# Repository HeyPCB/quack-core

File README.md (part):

# Quack Core

The brain board for the Open Duck Mini: a Pi Zero 2W carrier with the 14-servo STS bus, a fused and switched 2S power path laid in stitched copper zones, USB-C charging with balancing, and the IMU.

Part of [HeyPCB's open robot boards](https://github.com/HeyPCB). Designed end to end with the HeyPCB method on
KiCad 10 (headless pipeline, Freerouting 2.4.1); every number below is measured on the files in this repository.
Mentions of `./run.sh`, `docs/rules/`, `blocks/` or `parts/` refer to the heypcb-kicad SDK that produced them.

| Layers | Outline | Parts | Nets | Connections routed | Vias | ERC errors | DRC errors / unconnected / parity |
|---|---|---|---|---|---|---|---|
| 4 | 101 x 51.5 mm | 138 | 78 | 312 -> 0 open | 224 | 0 | 0 / 0 / 0 |

**Not fabricated, assembled or powered.**

| | |
|---|---|
| KiCad project | [`kicad/`](kicad/) |
| Gerbers (unzipped and zipped), BOM, CPL, STEP, schematic PDF | [`fab/`](fab/) |
| Printed parts (STEP/STL), CadQuery source, fit report | [`cad/`](cad/) |
| Renders | [top](media/top.png), [bottom](media/bottom.png) |
| Design process, every step as KiCad rendered it | [`media/design-process.mp4`](media/design-process.mp4) |

Quack Core is a brain board for the Open Duck Mini (v2), the open-source miniature biped by Antoine
Pirrone and contributors. It is a carrier for a Raspberry Pi Zero 2 W and it bolts onto the four
existing `trunk_top` bosses in the duck's rear bay. It takes the 2S pack through a 20 A fuse, a
1 mOhm shunt and a back-to-back P-FET switch, drives the STS3215 servo bus, and charges and balances
the pack from USB-C. It was designed with the HeyPCB method on KiCad 10 (10.0.6), by heypcb-kicad's
headless pipeline with Freerouting 2.4.1, from the brief in `board.json` and the research spec
`robots/research/duck/spec.md` (Option A).

**This board has not been fabricated, assembled or powered.** Everything below is what KiCad, the
pipeline and the CAD scripts measured on the design files. Nothing here has been tested on
hardware or in the robot, and nothing here contains or tests software.

## Specs

- **Pi Zero 2 W carrier.** The Pi plugs in face-up on a 2x20 SMD socket (PM254-2-20-S-8.5,
  C3975165), 8.5 mm tall, on four M2.5 standoffs (not supplied) on its 58 x 23 mm hole pattern.
  The board's 5.1 V back-powers the Pi through header pins 2 and 4. Do not also plug the Pi's PWR
  micro-USB.
- **Pack input:** a vertical XT30 (J2), an SMAJ10CA bidirectional TVS (D1), a 20 A Littelfuse
  NANO2 (F1, 0451020.MRL) and a 1 mOhm 3 W 2512 shunt (R1). An INA226 at 0x40 reads the shunt and
  the pack voltage; its ALERT goes to GPIO4 and to the servo-kill latch.
- **Main switch:** two AON6411 P-FETs, source to source (Q1, Q2). The robot's existing backpack
  slide switch is re-used as a logic switch on J5 and carries about 80 uA. A reversed pack leaves
  both FETs off.
- **Servo power:** a third AON6411 (Q3) switches VSYS onto VSERVO. It is on by default: GPIO26 (with
  a 100 k pull-down) or a latched INA226 ALERT turns it off. VSERVO has 2 x 470 uF / 16 V bulk
  (C10, C11) and 10 uF plus an ESD5Z5.0 on DATA at each port.
- **Servo bus:** an exact copy of the Waveshare Bus Servo Adapter (A) / Feetech reference half-duplex
  driver (74LVC1G126 + 74LVC1G125 + MMBT3906) on the Pi's PL011 UART (GPIO14/15), with the
  spec's additions: 0 ohm source-select links, a J16 header for an external USB-UART, a DNP RTS
  link, a DNP DATA pull-up and four DNP test pads.
- **Servo ports:** four 5264-type 3-pin headers (HC-5264-3A, C2845815), DATA / VSERVO / GND: J6 left
  leg, J7 right leg, J8 neck chain, J9 spare.
- **Pi rail:** an LM74700 + AO3400A ideal diode with 470 uF hold-up behind the 5 A face/aux fuse
  (F2), then a TPS56339 3 A buck to 5.10 V (53.6 k / 10 k on a 0.802 V reference) and an XC6206
  3.3 V LDO for the board's logic.
- **Charger:** BQ25887 2S boost charger from USB-C (J4, HRO TYPE-C-31-M-12, 5.1 k on each CC, a plain
  sink) through a 2 A PTC (F4), with cell balancing through the balance lead's mid tap (J3 pin 2).
  Input limit 1.48 A (750 ohm on ILIM). It taps the pack ahead of the switch through a 5 A NANO2
  (F3), so it charges with the robot switched off. Orange CHG LED, /INT to GPIO16.
- **IMU:** BNO055 at 0x28 (fitted) and a BMI088 footprint at 0x18/0x68 (not fitted).
- **Face link** (the shared contract with the Quack Face board, spec 4.5): J12 JST-GH 12P top entry,
  J13 JST-XH 2P with the fused battery rail.
- **Other I/O:** foot switches on J10/J11 (JST-PH 2P, 1 k / 100 nF RC and ESD), a Qwiic port (J14,
  JST-SH 4P top entry, 3.3 V), green 5V LED, red LED1/LED2 on GPIO5/GPIO6.
- **Board:** 101 x 51.5 mm (CAD x -93.5 to -42.0, y -50.5 to +50.5), 1.6 mm, 4 copper layers.
  F.Cu signal with a GND pour, In1 a GND plane, In2 signal with a VSERVO pour, B.Cu signal with a
  GND pour, and the power path laid as stitched copper zones on F.Cu, In2 and B.Cu (see *Power
  zones*). Single-sided assembly. Four non-plated 2.7 mm holes for M2.5 screws on the bosses, and
  four more for the Pi's standoffs. The front edge is notched 0.8 mm between CAD y -28.25 and
  +28.25 to clear the `trunk_top` chamfer (see *CAD fit*).

## Option A: the Pi moves into the body

Today the Pi Zero 2 W, its 5 V UBEC and the amplifier sit on the head's ceiling, and a harness
through the 4-DOF neck carries 7.4 V, USB, I2C and the foot-switch wires down to the body (spec
1.4). Quack Core takes the research spec's Option A (spec 2.6): the Pi plugs into this board, in the
body, next to the battery, the servo bus, the IMU and the foot switches. What that changes:

- **Update the URDF masses before retraining.** The Pi (about 10 g) and the UBEC (about 15 g,
  replaced here by the on-board buck) leave the head and join the trunk. Both figures are the
  spec's estimates. The walk policy was trained on the URDF's mass properties (`head_assembly`
  352.6 g, `trunk_assembly` 698.5 g), so update both links, add this board's own mass to the trunk,
  and retrain (spec 2.6, 7). This board's mass was not measured.
- **Camera.** CSI would have to cross the +/-160 degree head-yaw joint. Either run a round
  CSI-to-HDMI extension through the neck (Arducam B0091, with a 22-to-15-pin cable at the Pi), or
  leave the camera off. The walk runtime does not use it (spec 2.6).
- **Runtime: configuration only** (spec 3.10). No Python changes:
  1. `/boot/firmware/config.txt`: `enable_uart=1` and `dtoverlay=miniuart-bt`. The PL011 moves to
     GPIO14/15 and Bluetooth stays up for the gamepad. 1 Mbps is 48 MHz / 16 / 3 exactly.
  2. `cmdline.txt`: remove `console=serial0,115200`.
  3. A udev rule, `KERNEL=="ttyAMA0", SYMLINK+="ttyACM0"`, so the hard-coded `/dev/ttyACM0` in
     the runtime still opens the bus (or edit those defaults).
  4. Keep `dtparam=i2c_arm=on`. If the BNO055 reads glitch, apply Adafruit's `i2c_arm_baudrate`
     fix for its clock stretching.
  5. Keep the I2S amplifier overlay. Every GPIO number the runtime uses is unchanged.
- **The neck harness** becomes J12 (12 signals), J13 (the fused battery rail for the face board's
  own 5 V) and the neck servo chain on J8.
- **Wi-Fi and Bluetooth** move inside the PLA body, next to the cells. The spec estimates this as
  acceptable but slightly worse.
- **No first-hand report** of an STS3215 bus on a Pi's GPIO UART at 1 Mbps was found (spec 3.10).
  J16 and two 0 ohm links are the fallback: remove R17 and R18 and drive the same buffer from a
  3.3 V USB-UART on J16 (1 GND, 2 TXD into the board, 3 RXD out of it).

## Pinouts

### Pi Zero 2 W header (J1)

The 2x20 socket's footprint is the mirror image of the Pi's header (socket pad 2n-1 meets Pi pin
2n), so the block wires each socket pad to the net of the Pi pin it meets. The table is in Pi pin
numbers. Every GPIO number the walk runtime uses is the one it uses today (spec 3.8).

| Pi pin | GPIO | Net | Pi pin | GPIO | Net |
|---|---|---|---|---|---|
| 1 | 3V3 out | not connected | 2 | 5V | 5V (board's 5.10 V in) |
| 3 | GPIO2 | I2C_SDA | 4 | 5V | 5V |
| 5 | GPIO3 | I2C_SCL | 6 | GND | GND |
| 7 | GPIO4 | INA_ALERT | 8 | GPIO14 | UART_TX (servo bus) |
| 9 | GND | GND | 10 | GPIO15 | UART_RX (servo bus) |
| 11 | GPIO17 | UART_RTS (DNP link to TXEN) | 12 | GPIO18 | I2S_BCLK |
| 13 | GPIO27 | FOOT_R | 14 | GND | GND |
| 15 | GPIO22 | FOOT_L | 16 | GPIO23 | EYE_R |
| 17 | 3V3 out | not connected | 18 | GPIO24 | EYE_L |
| 19, 21, 23 | GPIO10, 9, 11 | not connected | 20 | GND | GND |
| 25 | GND | GND | 22 | GPIO25 | PROJ |
| 27, 28 | GPIO0, 1 (ID EEPROM) | not connected | 24, 26 | GPIO8, 7 | not connected |
| 29 | GPIO5 | LED1 | 30 | GND | GND |
| 31 | GPIO6 | LED2 | 32 | GPIO12 | ANT_R |
| 33 | GPIO13 | ANT_L | 34 | GND | GND |
| 35 | GPIO19 | I2S_LRCLK | 36 | GPIO16 | CHG_INT |
| 37 | GPIO26 | SERVO_KILL | 38 | GPIO20 | I2S_DIN |
| 39 | GND | GND | 40 | GPIO21 | I2S_DOUT |

I2C1 carries the BNO055 (0x28), the INA226 (0x40), the BQ25887 (0x6A or 0x6B, see *Check before
ordering*), the BMI088 footprint (0x18 / 0x68) and the Qwiic port. The board adds no I2C pull-ups:
the Pi's own pull-ups on GPIO2/3 serve the bus.

### Face link: J12 and J13 (the contract with Quack Face)

Both match the Quack Face board (commit 250de3c on `robot-quack-face`), whose harness runs pin n
to pin n.

**J12**, JST-GH 12-pin top entry, BM12B-GHS-TBT (C2983891), spec 4.5 unchanged:

| Pin | Net | Pin | Net |
|---|---|---|---|
| 1 | GND | 7 | GND |
| 2 | I2S_BCLK (GPIO18) | 8 | EYE_L (GPIO24) |
| 3 | GND | 9 | EYE_R (GPIO23) |
| 4 | I2S_LRCLK (GPIO19) | 10 | PROJ (GPIO25) |
| 5 | I2S_DOUT to the amplifier (GPIO21) | 11 | ANT_L (GPIO13) |
| 6 | I2S_DIN from the microphone (GPIO20) | 12 | ANT_R (GPIO12) |

The two mounting pads are on GND. The spec named the side-entry SM12B-GHS-TB. The board's front
edge sits 1.9 mm from `trunk_top`'s rear wall, so a side-entry plug facing forward could not be
inserted. The top-entry part has the same housing and pinout.

**J13**, JST-XH 2-pin (B2B-XH-A, C158012): **pin 1 VBAT** (VBAT_AUX, the pack after the main switch
and the 5 A fuse F2), **pin 2 GND**. F2 also feeds the Pi rail. The spec's face worst case (about
2.6 A at the pack) plus the Pi (about 1.4 A) is below 5 A.

### Other connectors

Positions are body centres, in the CAD frame of the print STLs (+x forward, +y the robot's left,
mm), read off the final board.

| Ref | Function | Part (LCSC) | Pin 1 / 2 / 3 | Centre (x, y) |
|---|---|---|---|---|
| J2 | Pack in | AMASS XT30UPB-M vertical (C428721) | - (GND, the chamfered end) / + (VBAT_IN) | (-87.3, -35.0) |
| J3 | Balance lead | JST-XH 3P B3B-XH-A (C144394) | not connected / mid tap / not connected | (-90.0, -44.0) |
| J4 | USB-C charge input | HRO TYPE-C-31-M-12 (C165948) | VBUS, CC1/CC2 5.1 k to GND, no data | (-62.0, -47.2), mouth 0.95 mm past the right edge |
| J5 | Backpack switch (logic) | JST-PH 2P (C131337) | SW_N / GND (closed = on) | (-90.5, +1.0) |
| J6 | Servo bus, left leg | HC-5264-3A (C2845815) | DATA / VSERVO / GND | (-45.3, +43.7) |
| J7 | Servo bus, right leg | HC-5264-3A | DATA / VSERVO / GND | (-45.3, -44.7) |
| J8 | Servo bus, neck chain | HC-5264-3A | DATA / VSERVO / GND | (-45.3, +32.5) |
| J9 | Servo bus, spare | HC-5264-3A | DATA / VSERVO / GND | (-90.4, +12.2) |
| J10 / J11 | Foot switch L / R | JST-PH 2P | switch (GPIO22 / GPIO27 through 1 k) / GND | (-74.0, +47.1) / (-90.5, -22.5) |
| J14 | Qwiic (3.3 V I2C1) | JST-SH 4P top entry BM04B-SRSS-TB (C160390) | GND / 3V3 / SDA / SCL | (-88.9, -7.8) |
| J16 | External UART for the bus | 1x3 2.54 mm (C2937625) | GND / TXD in / RXD out | (-89.5, +32.0) |

J2's polarity is the footprint's: KiCad's AMASS XT30UPB-M footprint prints - beside pad 1, at the
housing's chamfered end, and + beside pad 2, and the chamfered side of an XT30 is its negative
contact. Pad 2 (+) faces F1; pad 1 (-) is at the rear edge.

J3 uses only the balance lead's mid tap. Its B- pin is the cell side of the pack's BMS: tying it to
the board's ground would bypass the BMS's discharge FETs. So pins 1 and 3 are not connected.

## Power path and what the copper carries

```
J2 XT30 ─┬─ D1 SMAJ10CA ─ GND
         ├─ F3 5 A ─ BQ25887 BAT (charger, J4 USB-C, J3 mid tap)
         └─ F1 20 A ─ R1 1 mOhm (INA226 0x40) ─ Q1 ┐ AON6411 back to back, gates on J5
                                                Q2 ┘
                                                 │ VSYS
              ┌──────────────────────────────────┼──────────────────────────┐
         Q3 AON6411 servo kill              F2 5 A ─ VBAT_AUX ─ J13 (face)    R8 / Q4 / Q5 gate drive
         (GPIO26, INA226 ALERT)                      └─ LM74700 + AO3400A ─ 470 uF ─ TPS56339 5.10 V ─ Pi pins 2/4
              │ VSERVO                                                               └─ XC6206 3.3 V
         C10, C11 470 uF; J6, J7, J8, J9 (10 uF + ESD5Z each)
```

The pack current runs in a straight column down the board's right side: the XT30 at the rear, then
F1, R1, Q1, Q2 and Q3 one above the other, with Q3's drain at the front, beside C10 and J7. The
FETs face source row to source row, so QS and VSYS are three short stubs each.

**Net classes** (from the brief; a class with a current is never narrowed by the routing ladder):
BATT 3.0 mm (VBAT_IN, VBAT_F, VBAT_SH), FETLINK 1.2 mm (QS, VSYS, limited by the AON6411's 0.5 mm
source leads), SERVO 2.5 mm with 2.2 / 1.2 mm vias (VSERVO), AUX 0.8 mm (VBAT_AUX, VPI_IN, 5V,
BUCK_SW), USBPWR 0.6 mm (VBUS), CHG 0.4 mm (the charger's power nets). The tracks only connect the
path; the current is carried by the zones below.

### Power zones

After routing reaches 0 open, the pour stage lays the brief's `board.zones`: each a named net's
copper over a region on chosen layers, above the plan pours, with every pad joined solid (no
thermal spokes), and, where the zone has a `stitch` pitch, its own via lattice. Board coordinates
are mm from the outline's top-left corner; every reason is also in `board.json`.

| Zone | Net | Layers | Region | Vias (0.6 / 0.3 mm, 1.2 mm pitch) |
|---|---|---|---|---|
| `vbat_in` | VBAT_IN | F.Cu, B.Cu | J2's + pad, F1's input pad, F3 and the TVS (x 79-93, y 35.75-45.25) | 13 |
| `vbat_f` | VBAT_F | F.Cu, B.Cu | F1's output pad to the shunt (x 79.9-90.2, y 27.9-35.6), stepped round the Pi standoff at (79.5, 35.5) | 12 |
| `vbat_sh` | VBAT_SH | F.Cu, B.Cu | the shunt to Q1's drain (x 79.9-90.2, y 18.45-27.75) | 9 |
| `qs` | QS | F.Cu | the 0.7 mm gap between Q1's and Q2's source rows (x 79.9-88.3, y 15.65-18.15) | none: no via fits outside the FETs' courtyards |
| `vsys` | VSYS | F.Cu, B.Cu | Q2's drain to Q3's sources, F2 and R8 (x 82.6-94.5, y 8.8-15.45) | 7 |
| `vservo_q3` | VSERVO | F.Cu, In2 | Q3's drain to C10, J7's V pin and C7 (x 67.6-97.6, y 0.85-9.7), J7's DATA and GND pins left out | 26 |
| `vservo_q3_b` | VSERVO | B.Cu | Q3's corner on B.Cu, stopping at x 90.6 | (shares `vservo_q3`'s) |
| `vservo_band_in2`, `vservo_band_b` | VSERVO | In2; B.Cu | along the front edge to C11, J8 and J6; on B.Cu also under the Pi socket (y to 16.6) | none (a lattice there would perforate In1's GND under the ports) |
| `gnd` | GND | F.Cu, B.Cu | the whole board under the zones above | 55, at 4 mm |

The `gnd` zone exists to join the XT30's - pad and the ports' GND pins solid. Any GND zone makes
the plan's GND stitcher place nothing (it wants each via's ring inside every GND fill), so the
`gnd` zone stitches GND itself; the plan's own stitching count reads 0. J7's GND pin sits between
Q3 and J7's V pin, so on any one layer only one of the two nets can pass it: VSERVO reaches J7
on F.Cu and In2, and J7's GND leaves on B.Cu, down the right edge to the XT30.

### Measured copper on the current path

`copper.py` (KiCad's Python) lists every track, via and pour of each power net on the final board
and exports the copper (tracks, pads, plan pours and zones) as polygons. `copper_cut.py` (the
robots CAD environment, it needs scipy) rasterises that copper on a 0.1 mm grid and finds, for
each link of the path, the **narrowest cross-section the link's whole current must pass**: a
max-flow / min-cut from the link's source pads to its sink pads, over every layer, with tracks,
zones and via barrels together, in parallel. Outer copper is taken as 35 um, inner as 17.5 um
(JLCPCB's standard 4-layer build), via plating as 25 um. Each cut is rated with
`heypcb_kicad.route.ipc2221_amps` (IPC-2221, I = k dT^0.44 A^0.725), per layer, summed. Each link
is cut a second time with the copper within 1 mm of its pads counted as the pads ("beyond the
pads"): that rates the board's own copper between the parts, apart from the parts' fixed lands.

| Link | From, to | Narrowest cross-section (35 um equivalent) | 10 C rise | **20 C rise** | Beyond the pads, 10 C / 20 C |
|---|---|---|---|---|---|
| VBAT_IN | J2 pad 2 to F1.1 | 8.75 mm: F.Cu 6.73, via barrels 2.02 | 13.5 A | **18.3 A** | 15.3 A / 20.8 A |
| VBAT_F | F1.2 to R1.1 | 8.29 mm of F.Cu, at the fuse's output pad | 11.1 A | **15.0 A** | pads 0.9 mm apart |
| VBAT_SH | R1.2 to Q1 drain | 8.38 mm: F.Cu 7.71, a barrel 0.67 | 12.3 A | **16.7 A** | pads 0.9 mm apart |
| QS | Q1 sources to Q2 sources | 3.71 mm of F.Cu: the 0.7 mm gap between the two rows of 0.5 mm source leads | 6.2 A | **8.4 A** | leads 0.7 mm apart |
| VSYS | Q2 drain to Q3 sources | 4.19 mm of F.Cu, at Q3's three source leads | 6.8 A | **9.2 A** | pads 0.7 mm apart |
| VSERVO, all ports | Q3 drain to J6-J9 pin 2 | 13.00 mm: F.Cu 2.41, In2 1.43, B.Cu 9.17 | 18.0 A | **24.4 A** | 18.9 A / 25.7 A |
| VSERVO, right leg | Q3 drain to J7.2 | 3.84 mm: F.Cu 2.41, In2 1.43 | 6.1 A | **8.2 A** | 7.0 A / 9.5 A |
| VSERVO, left leg + neck | Q3 drain to J6.2, J8.2 | 8.65 mm: In2 1.79, B.Cu 6.86 | 11.5 A | **15.6 A** | 11.5 A / 15.6 A |
| VSERVO, spare | Q3 drain to J9.2 | 2.66 mm: In2 0.35, B.Cu 2.31 (its routed track) | 4.9 A | **6.7 A** | 4.9 A / 6.7 A |
| GND, all ports | J6-J9 pin 3 to J2 pad 1 | 11.75 mm: F.Cu 4.05, In1 0.65, In2 0.07, B.Cu 6.99 | 17.4 A | **23.7 A** | 21.3 A / 28.9 A |
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
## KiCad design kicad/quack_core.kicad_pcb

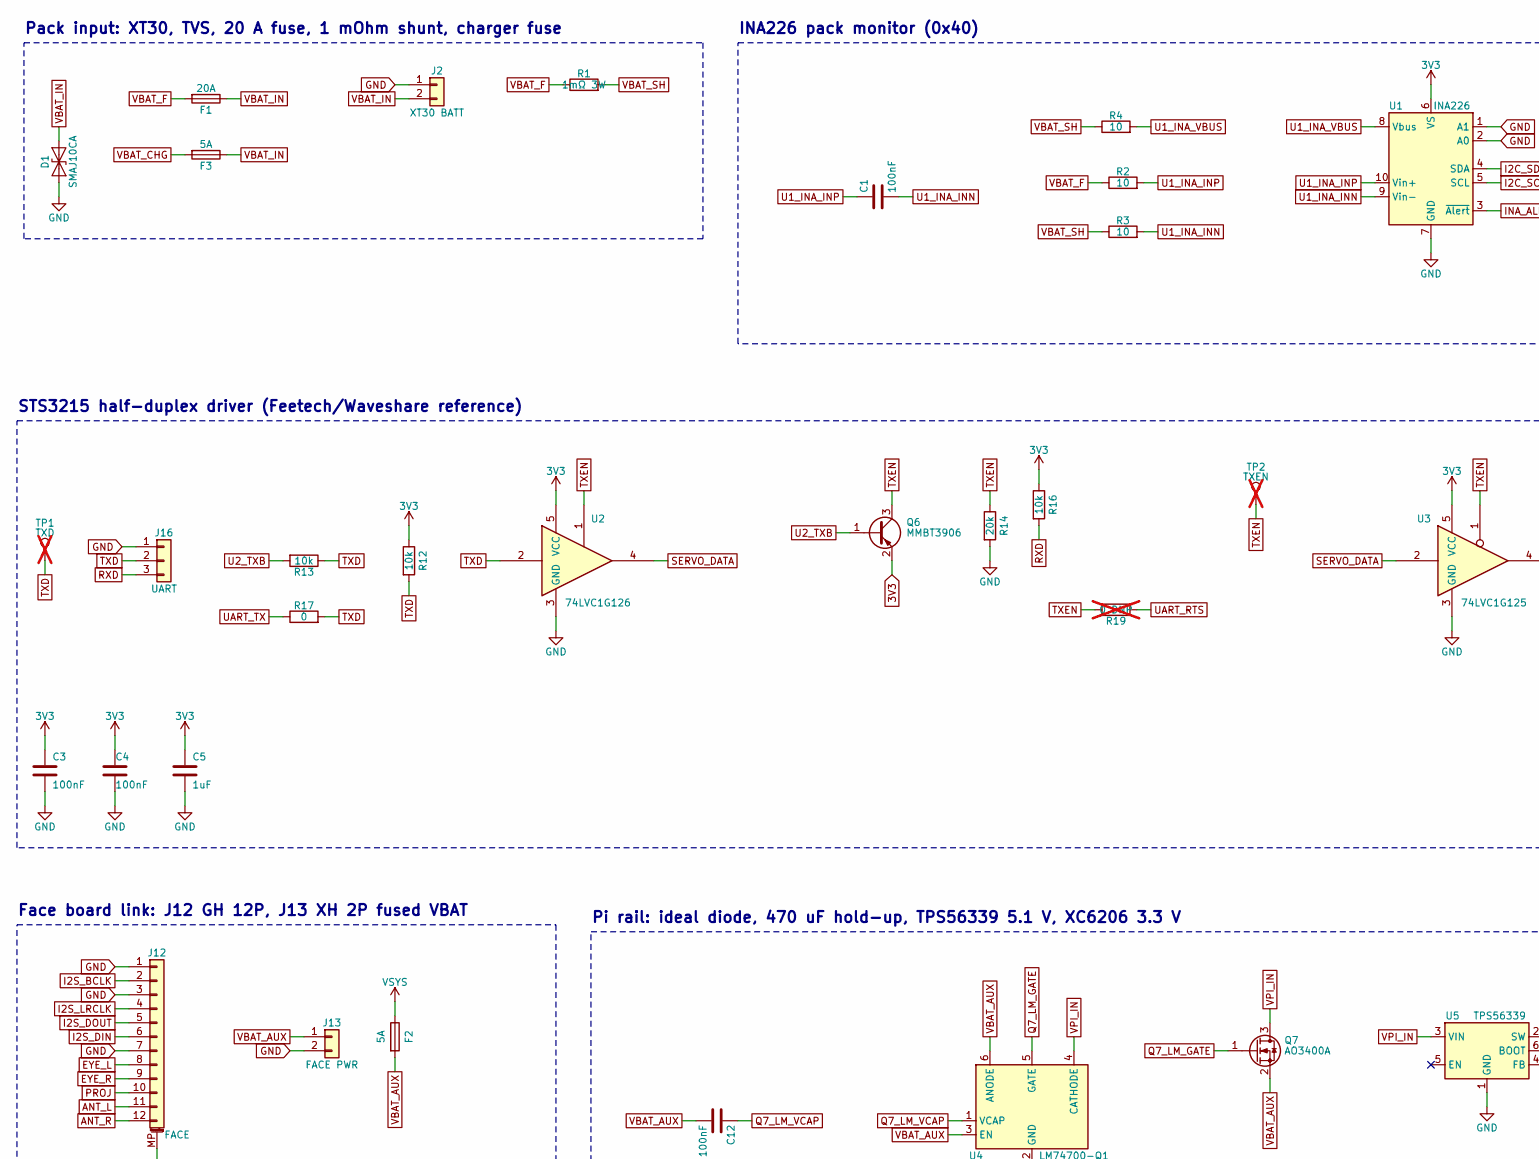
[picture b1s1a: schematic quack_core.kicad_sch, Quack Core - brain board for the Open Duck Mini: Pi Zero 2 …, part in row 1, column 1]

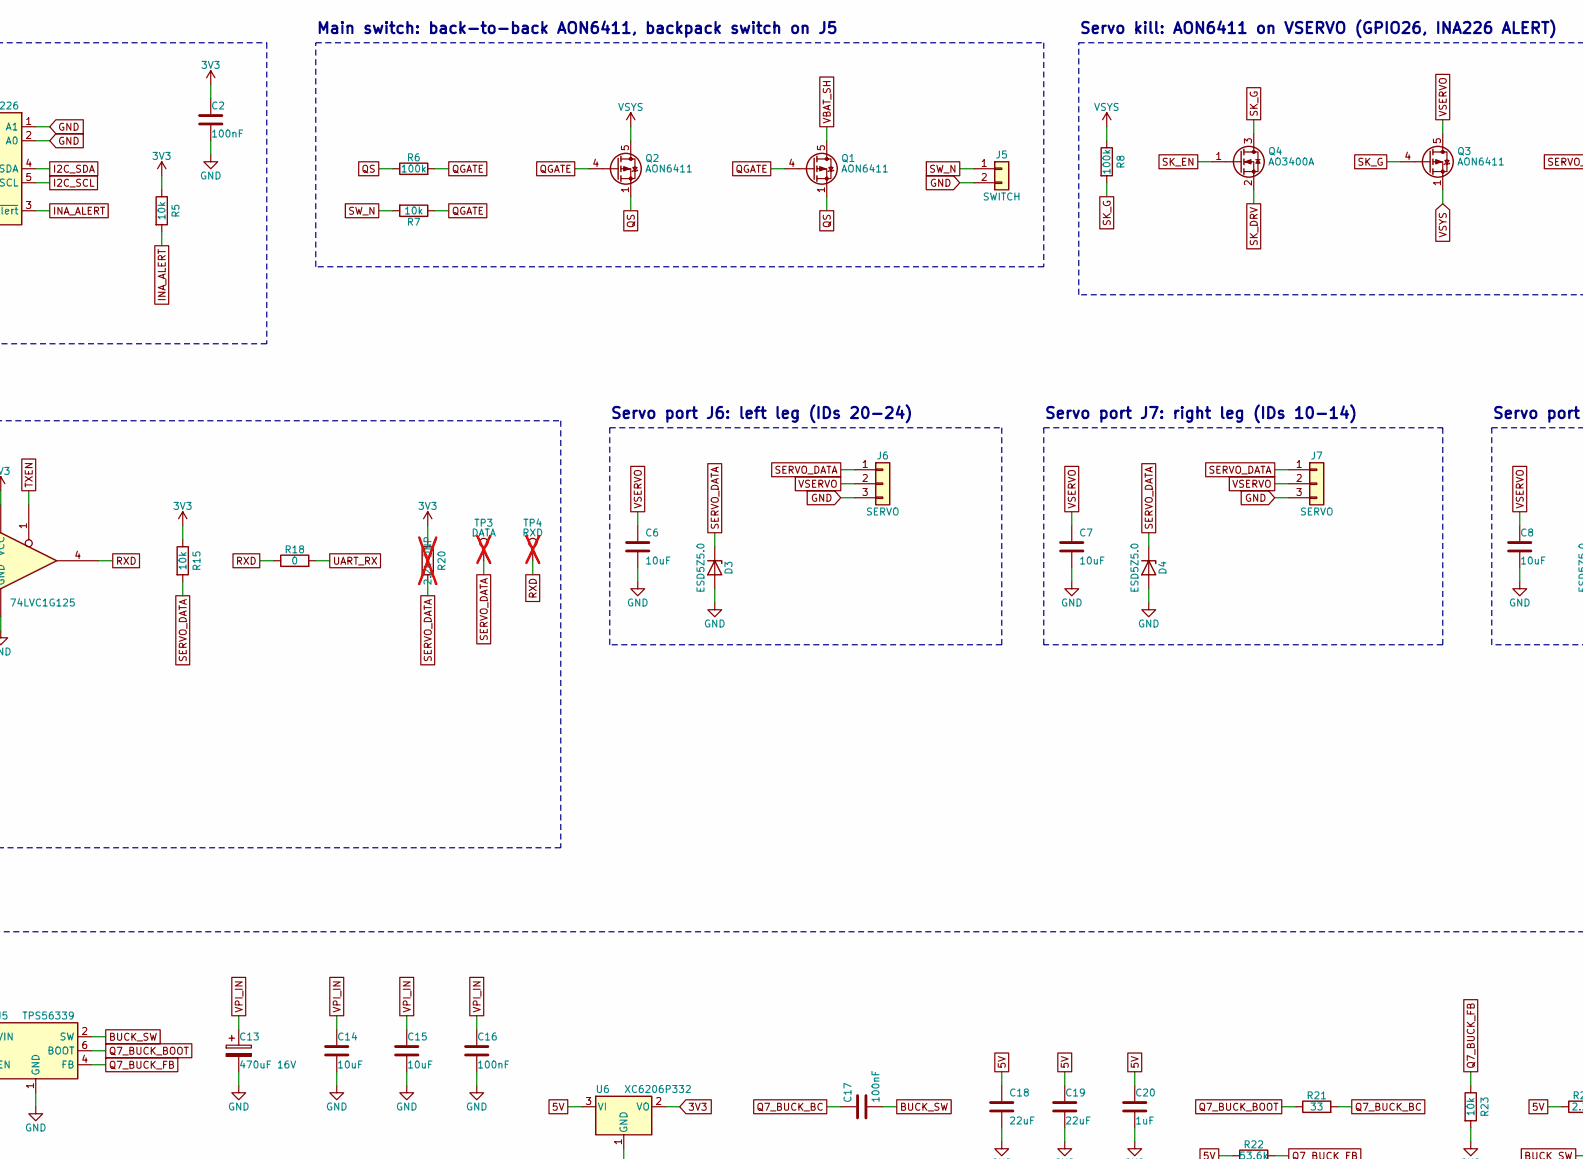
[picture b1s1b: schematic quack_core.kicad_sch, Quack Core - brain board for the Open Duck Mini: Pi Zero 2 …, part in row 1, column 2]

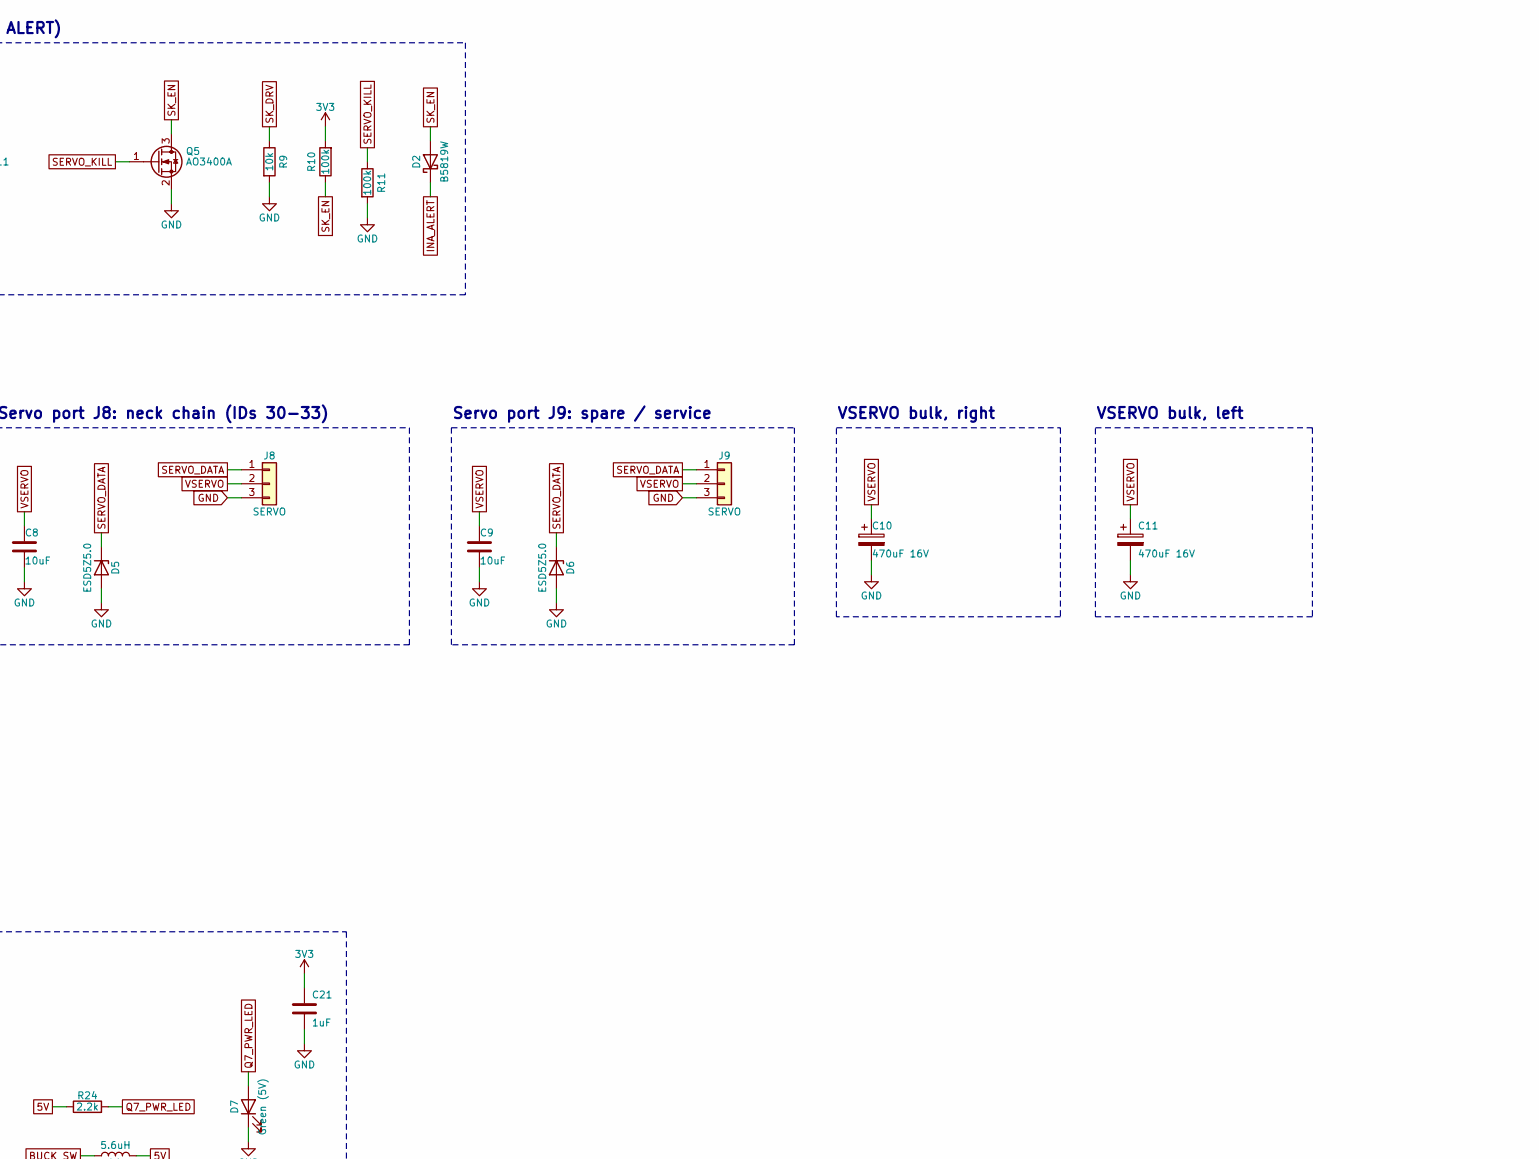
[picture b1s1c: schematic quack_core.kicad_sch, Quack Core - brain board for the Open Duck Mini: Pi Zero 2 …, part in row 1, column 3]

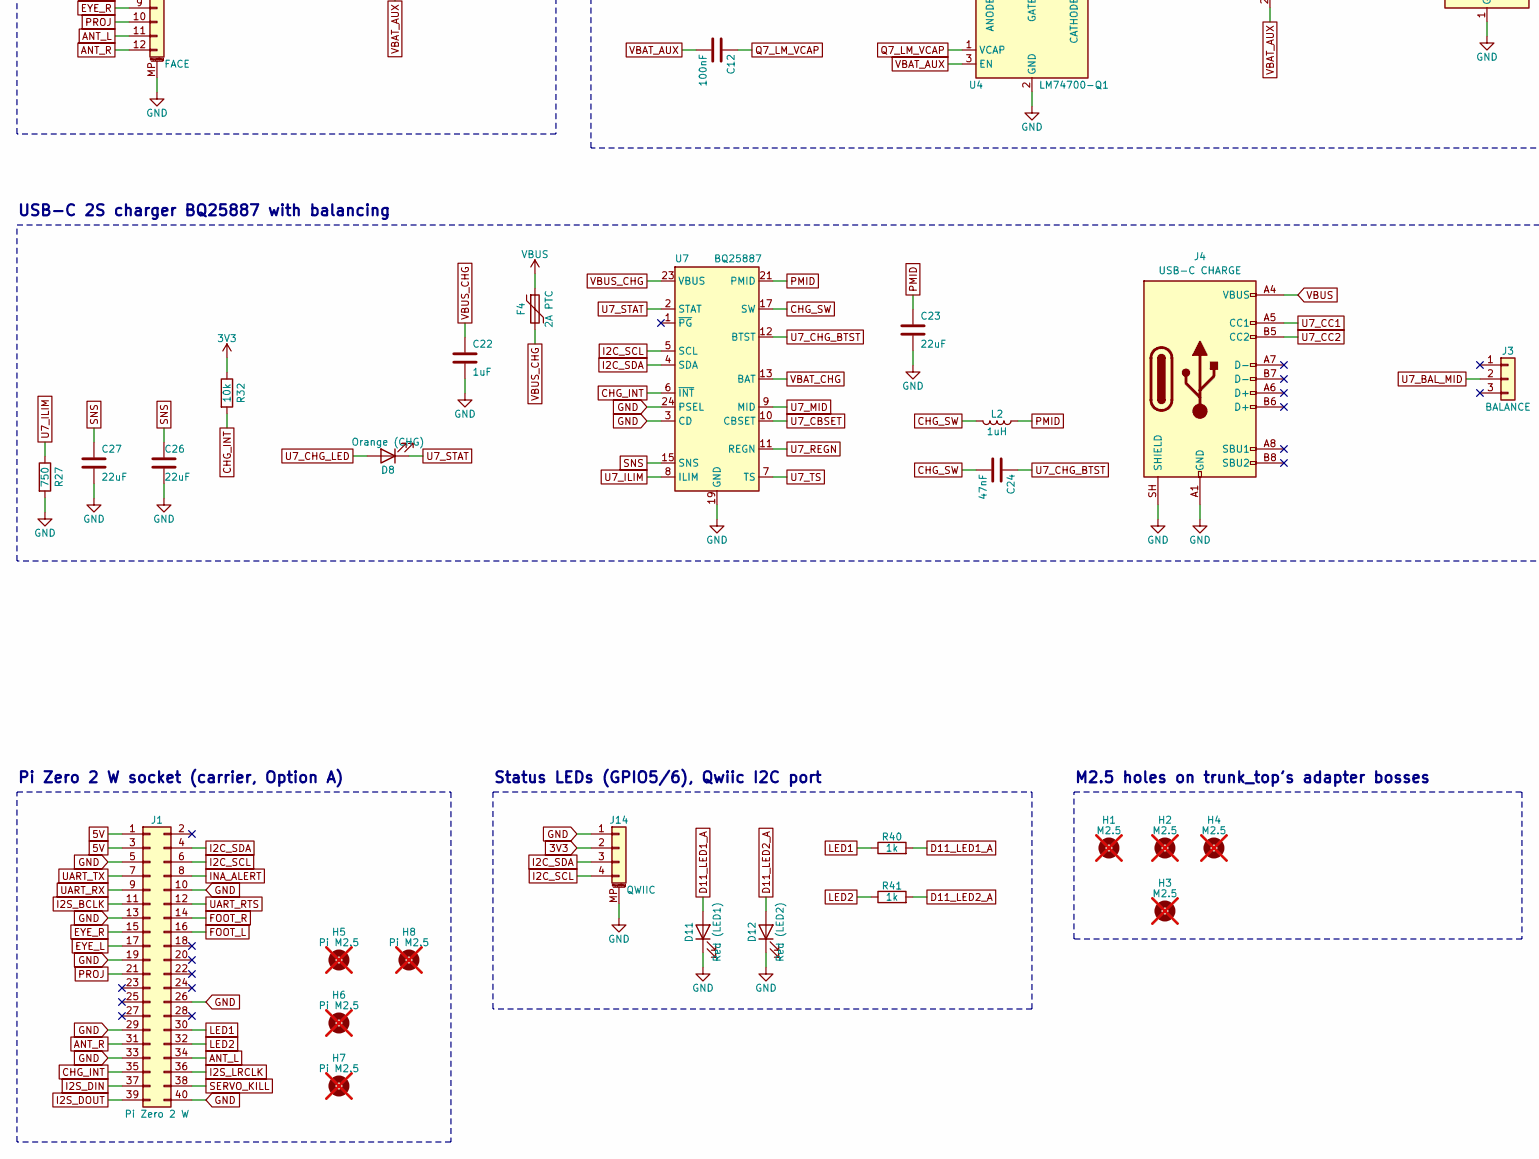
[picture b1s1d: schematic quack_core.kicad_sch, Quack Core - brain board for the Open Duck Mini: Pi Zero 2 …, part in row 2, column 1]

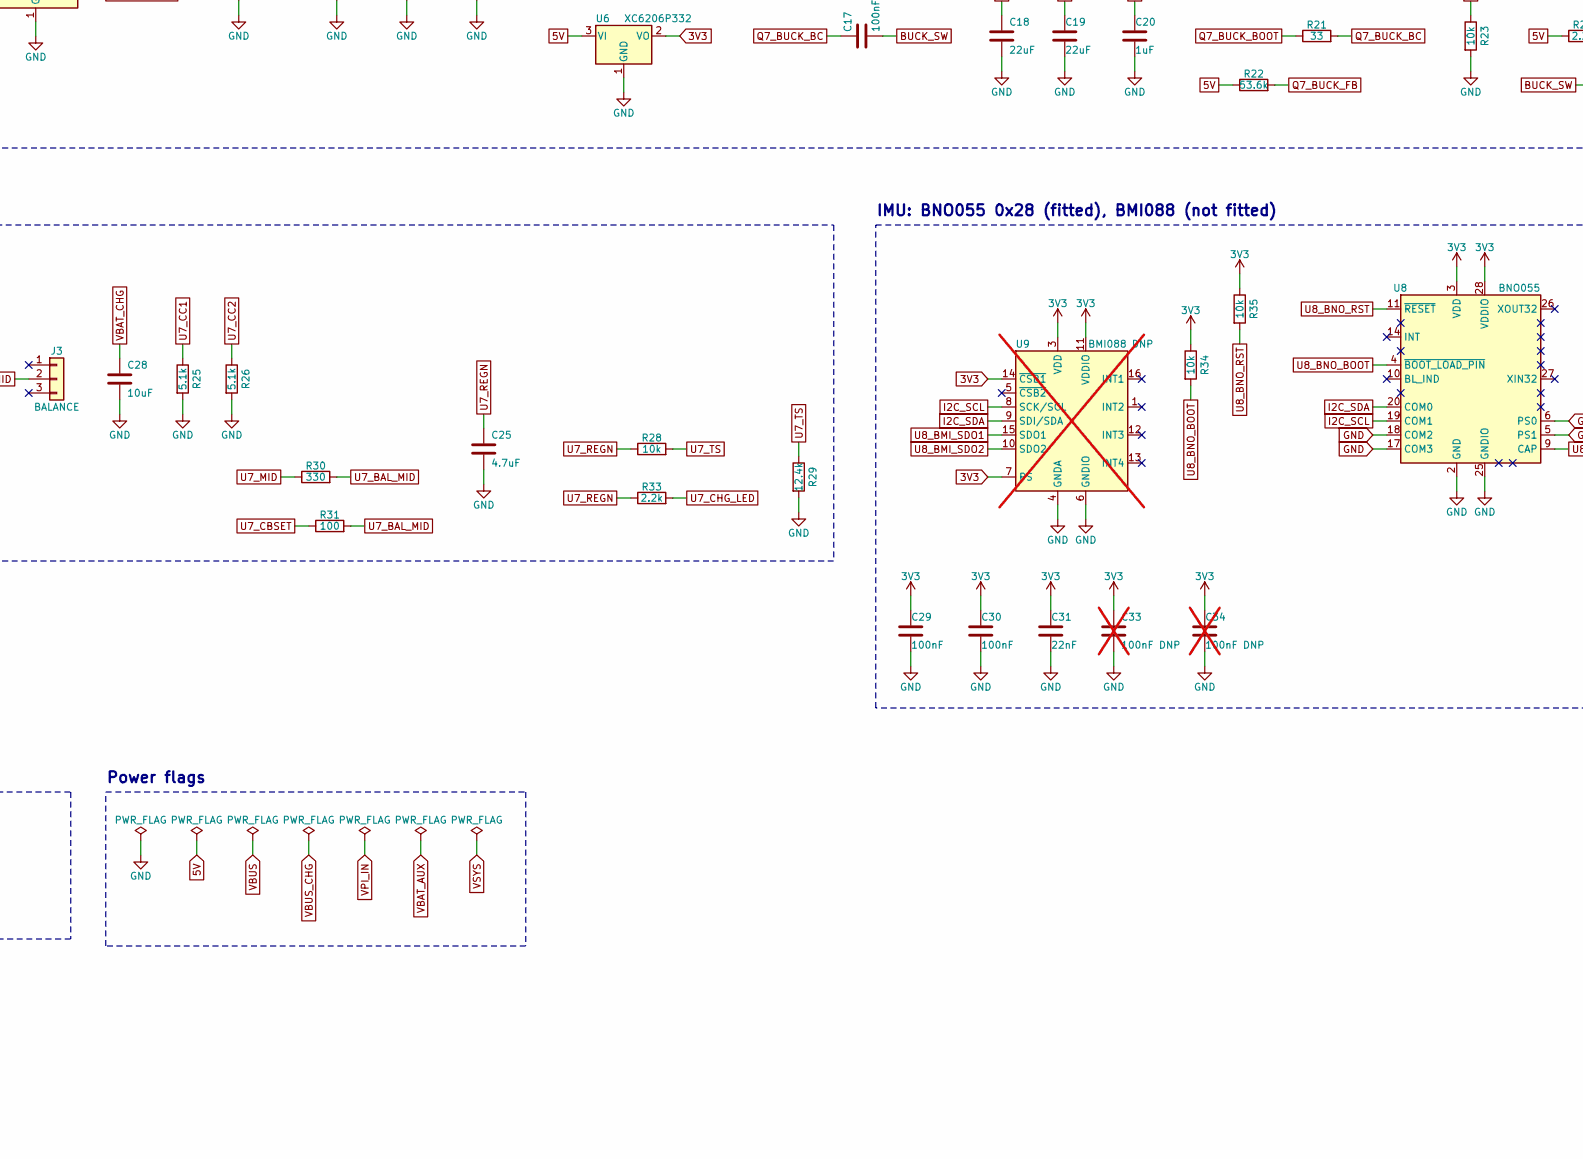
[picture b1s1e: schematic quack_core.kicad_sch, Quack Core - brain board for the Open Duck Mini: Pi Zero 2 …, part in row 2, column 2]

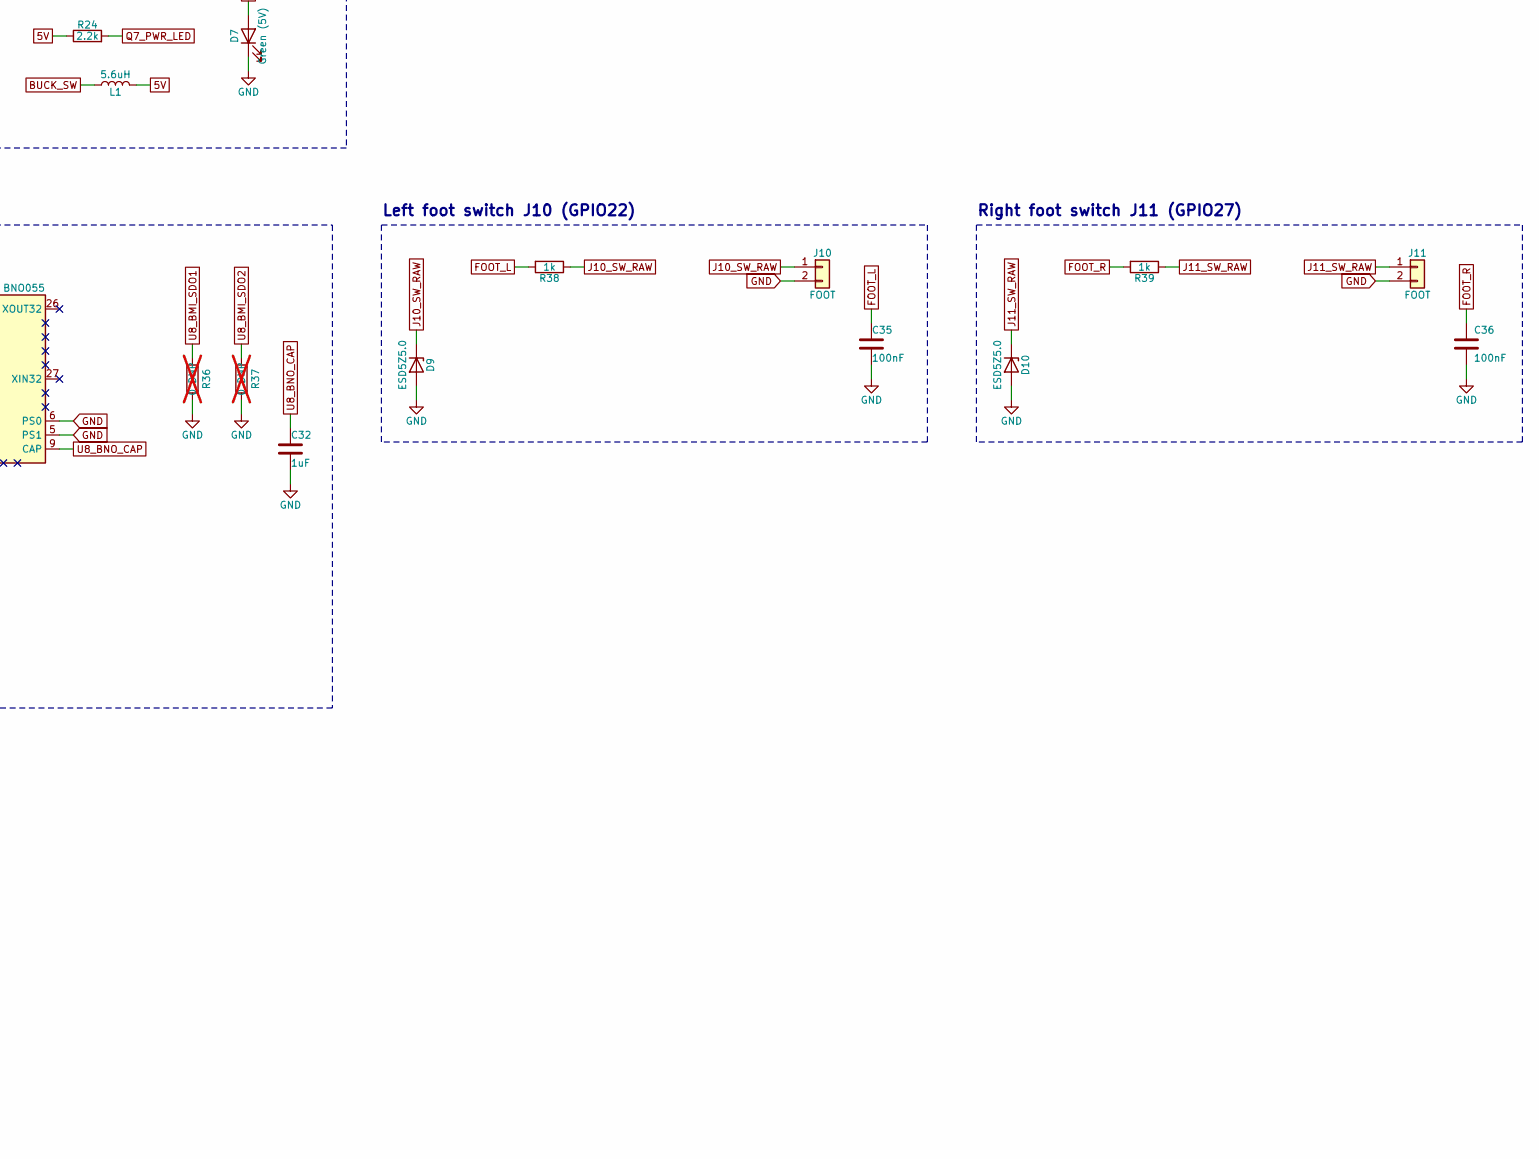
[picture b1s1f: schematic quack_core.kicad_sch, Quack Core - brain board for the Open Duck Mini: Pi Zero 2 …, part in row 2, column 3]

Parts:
C1, C2, C3, C4, C12, C16, C17, C29, C30, C35, C36: 100nF; C_0603_1608Metric; MPN CC0603KRX7R9BB104; LCSC C14663
C5, C20, C21, C22, C32: 1uF; C_0603_1608Metric; MPN CL10A105KB8NNNC; LCSC C15849
C6, C7, C8, C9: 10uF; C_1206_3216Metric; MPN CL31A106KBHNNNE; LCSC C13585
C10, C11, C13: 470uF 16V; CP_Elec_6.3x7.7; MPN RVT1C471M0607; LCSC C2977552
C14, C15, C28: 10uF; C_0805_2012Metric; MPN CL21A106KAYNNNE; LCSC C15850
C18, C19, C23, C26, C27: 22uF; C_0805_2012Metric; MPN CL21A226MAQNNNE; LCSC C45783
C24: 47nF; C_0603_1608Metric; MPN CL10B473KB8NNNC; LCSC C1622
C25: 4.7uF; C_0805_2012Metric; MPN CL21A475KAQNNNE; LCSC C1779
C31: 22nF; C_0603_1608Metric; MPN CL10B223KB8NNNC; LCSC C21122
C33, C34: 100nF DNP; C_0603_1608Metric; not fitted
D1: SMAJ10CA; D_SMA; MPN SMAJ10CA; LCSC C19077530
D2: B5819W; D_SOD-123; MPN B5819W SL; LCSC C8598
D3, D4, D5, D6, D9, D10: ESD5Z5.0; D_SOD-523; MPN ESD5Z5.0T1G; LCSC C82044
D7: Green (5V); LED_0603_1608Metric; MPN KT-0603G; LCSC C12624
D8: Orange (CHG); LED_0603_1608Metric; MPN XL-1608UOC-06; LCSC C965800
D11: Red (LED1); LED_0603_1608Metric; MPN KT-0603R; LCSC C2286
D12: Red (LED2); LED_0603_1608Metric; MPN KT-0603R; LCSC C2286
F1: 20A; Fuse_Littelfuse-NANO2-451_453; MPN 0451020.MRL; LCSC C178980
F2, F3: 5A; Fuse_Littelfuse-NANO2-451_453; MPN 0451005.MRL; LCSC C48467
F4: 2A PTC; Fuse_1206_3216Metric; MPN 1206L200/16NR; LCSC C22374899
H1, H2, H3, H4: M2.5; MountingHole_2.7mm_M2.5; not fitted
H5, H6, H7, H8: Pi M2.5; MountingHole_2.7mm_M2.5; not fitted
J1: Pi Zero 2 W; PinSocket_2x20_P2.54mm_Vertical_SMD; MPN PM254-2-20-S-8.5; LCSC C3975165
J2: XT30 BATT; AMASS_XT30UPB-M_1x02_P5.0mm_Vertical; MPN XT30UPB-M; LCSC C428721
J3: BALANCE; JST_XH_B3B-XH-A_1x03_P2.50mm_Vertical; MPN B3B-XH-A(LF)(SN); LCSC C144394
J4: USB-C CHARGE; USB_C_Receptacle_HRO_TYPE-C-31-M-12; MPN TYPE-C-31-M-12; LCSC C165948
J5: SWITCH; JST_PH_B2B-PH-K_1x02_P2.00mm_Vertical; MPN B2B-PH-K-S(LF)(SN); LCSC C131337
J6, J7, J8, J9: SERVO; Molex_SPOX_5267-03A_1x03_P2.50mm_Vertical; MPN HC-5264-3A; LCSC C2845815
J10, J11: FOOT; JST_PH_B2B-PH-K_1x02_P2.00mm_Vertical; MPN B2B-PH-K-S(LF)(SN); LCSC C131337
J12: FACE; JST_GH_BM12B-GHS-TBT_1x12-1MP_P1.25mm_Vertical; MPN BM12B-GHS-TBT(LF)(SN)(N); LCSC C2983891
J13: FACE PWR; JST_XH_B2B-XH-A_1x02_P2.50mm_Vertical; MPN B2B-XH-A(LF)(SN); LCSC C158012
J14: QWIIC; JST_SH_BM04B-SRSS-TB_1x04-1MP_P1.00mm_Vertical; MPN BM04B-SRSS-TB(LF)(SN); LCSC C160390
J16: UART; PinHeader_1x03_P2.54mm_Vertical; MPN PZ254V-11-03P; LCSC C2937625
L1: 5.6uH; L_Changjiang_FXL0630; MPN FXL0630-5R6-M; LCSC C475914
L2: 1uH; L_Coilcraft_XxL4020; MPN XFL4020-102MEC; LCSC C5355380
Q1, Q2, Q3: AON6411; AO_DFN-8-1EP_5.55x5.2mm_P1.27mm_EP4.12x4.6mm; MPN AON6411; LCSC C81007
Q4, Q5, Q7: AO3400A; SOT-23; MPN AO3400A; LCSC C20917
Q6: MMBT3906; SOT-23; MPN MMBT3906LT1G; LCSC C53444
R1: 1mΩ 3W; R_2512_6332Metric; MPN HoJLR2512-3W-1mR-1%; LCSC C2903470
R2, R3, R4: 10; R_1206_3216Metric; MPN 1206W4F100JT5E; LCSC C17903
R5, R7, R9, R12, R13, R15, R16, R23, R28, R32, R34, R35: 10k; R_0603_1608Metric; MPN FRC0603F1002TS; LCSC C2906982
R6, R8: 100k; R_1206_3216Metric; MPN 1206W4F1003T5E; LCSC C17900
R10, R11: 100k; R_0603_1608Metric; MPN 0603WAF1003T5E; LCSC C25803
R14: 20k; R_0603_1608Metric; MPN 0603WAF2002T5E; LCSC C4184
R17, R18: 0; R_0603_1608Metric; MPN 0603WAF0000T5E; LCSC C21189
R19, R36, R37: 0 DNP; R_0603_1608Metric; not fitted
R20: 2.2k DNP; R_0603_1608Metric; not fitted
R21: 33; R_0603_1608Metric; MPN 0603WAF330JT5E; LCSC C23140
R22: 53.6k; R_0603_1608Metric; MPN FRC0603F5362TS; LCSC C2930115
R24, R33: 2.2k; R_0603_1608Metric; MPN 0603WAF2201T5E; LCSC C4190
R25, R26: 5.1k; R_0402_1005Metric; MPN 0402WGF5101TCE; LCSC C25905
R27: 750; R_0603_1608Metric; MPN 0603WAF7500T5E; LCSC C23241
R29: 12.4k; R_0603_1608Metric; MPN FRC0603F1242TS; LCSC C2930060
R30: 330; R_0603_1608Metric; MPN 0603WAF3300T5E; LCSC C23138
R31: 100; R_1206_3216Metric; MPN 1206W4F1000T5E; LCSC C17901
R38, R39, R40, R41: 1k; R_0603_1608Metric; MPN 0603WAF1001T5E; LCSC C21190
TP1: TXD; TestPoint_Pad_D1.0mm; not fitted
TP2: TXEN; TestPoint_Pad_D1.0mm; not fitted
TP3: DATA; TestPoint_Pad_D1.0mm; not fitted
TP4: RXD; TestPoint_Pad_D1.0mm; not fitted
U1: INA226; TSSOP-10_3x3mm_P0.5mm; MPN INA226AIDGSR; LCSC C49851
U2: 74LVC1G126; SOT-23-5; MPN SN74LVC1G126DBVR; LCSC C7834
U3: 74LVC1G125; SOT-23-5; MPN SN74LVC1G125DBVR; LCSC C23654
U4: LM74700-Q1; SOT-23-6; MPN LM74700QDBVRQ1; LCSC C2941042
U5: TPS56339; SOT-23-6; MPN TPS56339DDCR; LCSC C2071106
U6: XC6206P332; SOT-23-3; MPN XC6206P332MR-G; LCSC C5446
U7: BQ25887; Texas_RGE0024H_VQFN-24-1EP_4x4mm_P0.5mm_EP2.7x2.7mm; MPN BQ25887RGER; LCSC C2761614
U8: BNO055; LGA-28_5.2x3.8mm_P0.5mm; MPN BNO055; LCSC C93216
U9: BMI088 DNP; Bosch_LGA-16_4.5x3mm_P0.5mm_LayoutBorder7x1y_ClockwisePinNu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; MPN BMI088; LCSC C194919; not fitted

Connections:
3V3: C2.1, C3.1, C4.1, C5.1, C21.1, C29.1, C30.1, C31.1, C33.1, C34.1, J14.2, Q6.2 (E), R5.1, R10.2, R12.1, R15.1, R16.1, R20.1, R32.1, R34.1, R35.1, U1.6 (VS), U2.5 (VCC), U3.5 (VCC), U6.2 (VO), U8.3 (VDD), U8.28 (VDDIO), U9.3 (VDD), U9.7 (PS), U9.11 (VDDIO), U9.14 (~CSB1)
5V: C18.1, C19.1, C20.1, J1.1, J1.3, L1.2, R22.1, R24.1, U6.3 (VI)
ANT_L: J1.34, J12.11
ANT_R: J1.31, J12.12
BUCK_SW: C17.2, L1.1, U5.2 (SW)
CHG_INT: J1.35, R32.2, U7.6 (~INT)
CHG_SW: C24.2, L2.2, U7.17 (SW), U7.18 (SW)
D11_LED1_A: D11.2 (A), R40.2
D11_LED2_A: D12.2 (A), R41.2
EYE_L: J1.17, J12.8
EYE_R: J1.15, J12.9
FOOT_L: C35.1, J1.16, R38.2
FOOT_R: C36.1, J1.14, R39.2
GND: C2.2, C3.2, C4.2, C5.2, C6.2, C7.2, C8.2, C9.2, C10.2, C11.2, C13.2, C14.2, C15.2, C16.2, C18.2, C19.2, C20.2, C21.2, C22.2, C23.2, C25.2, C26.2, C27.2, C28.2, C29.2, C30.2, C31.2, C32.2, C33.2, C34.2, C35.2, C36.2, D1.1 (A1), D3.2 (A), D4.2 (A), D5.2 (A), D6.2 (A), D7.1 (K), D9.2 (A), D10.2 (A), D11.1 (K), D12.1 (K), J1.5, J1.10, J1.13, J1.19, J1.26, J1.29, J1.33, J1.40, J2.1, J4.A1 (GND), J4.A12 (GND), J4.B1 (GND), J4.B12 (GND), J4.SH (SHIELD), J5.2, J6.3, J7.3, J8.3, J9.3, J10.2, J11.2, J12.1, J12.3, J12.7, J12.MP (MountPin), J13.2, J14.1, J14.MP (MountPin), J16.1, Q5.2 (S), R9.2, R11.2, R14.2, R23.2, R25.2, R26.2, R27.2, R29.2, R36.2, R37.2, U1.1 (A1), U1.2 (A0), U1.7 (GND), U2.3 (GND), U3.3 (GND), U4.2 (GND), U5.1 (GND), U6.1 (GND), U7.3 (CD), U7.19 (GND), U7.20 (GND), U7.24 (PSEL), U7.25 (GND), U8.2 (GND), U8.5 (PS1), U8.6 (PS0), U8.17 (COM3), U8.18 (COM2), U8.25 (GNDIO), U9.2 (GNDA), U9.4 (GNDA), U9.6 (GNDIO)
I2C_SCL: J1.6, J14.4, U1.5 (SCL), U7.5 (SCL), U8.19 (COM1), U9.8 (SCK/SCL)
I2C_SDA: J1.4, J14.3, U1.4 (SDA), U7.4 (SDA), U8.20 (COM0), U9.9 (SDI/SDA)
I2S_BCLK: J1.11, J12.2
I2S_DIN: J1.37, J12.6
I2S_DOUT: J1.39, J12.5
I2S_LRCLK: J1.36, J12.4
INA_ALERT: D2.1 (K), J1.8, R5.2, U1.3 (~Alert)
J10_SW_RAW: D9.1 (K), J10.1, R38.1
J11_SW_RAW: D10.1 (K), J11.1, R39.1
LED1: J1.30, R40.1
LED2: J1.32, R41.1
PMID: C23.1, L2.1, U7.21 (PMID), U7.22 (PMID)
PROJ: J1.21, J12.10
Q7_BUCK_BC: C17.1, R21.2
Q7_BUCK_BOOT: R21.1, U5.6 (BOOT)
Q7_BUCK_FB: R22.2, R23.1, U5.4 (FB)
Q7_LM_GATE: Q7.1 (G), U4.5 (GATE)
Q7_LM_VCAP: C12.1, U4.1 (VCAP)
Q7_PWR_LED: D7.2 (A), R24.2
QGATE: Q1.4 (G), Q2.4 (G), R6.2, R7.1
QS: Q1.1 (S), Q1.2 (S), Q1.3 (S), Q2.1 (S), Q2.2 (S), Q2.3 (S), R6.1
RXD: J16.3, R16.2, R18.1, TP4.1, U3.4
SERVO_DATA: D3.1 (K), D4.1 (K), D5.1 (K), D6.1 (K), J6.1, J7.1, J8.1, J9.1, R15.2, R20.2, TP3.1, U2.4, U3.2
SERVO_KILL: J1.38, Q5.1 (G), R11.1
SK_DRV: Q4.2 (S), R9.1
SK_EN: D2.2 (A), Q4.1 (G), Q5.3 (D), R10.1
SK_G: Q3.4 (G), Q4.3 (D), R8.2
SNS: C26.1, C27.1, U7.15 (SNS), U7.16 (SNS)
SW_N: J5.1, R7.2
TXD: J16.2, R12.2, R13.1, R17.2, TP1.1, U2.2
TXEN: Q6.3 (C), R14.1, R19.2, TP2.1, U2.1, U3.1
U1_INA_INN: C1.2, R3.2, U1.9 (Vin-)
U1_INA_INP: C1.1, R2.2, U1.10 (Vin+)
U1_INA_VBUS: R4.2, U1.8 (Vbus)
U2_TXB: Q6.1 (B), R13.2
U7_BAL_MID: J3.2, R30.2, R31.2
U7_CBSET: R31.1, U7.10 (CBSET)
U7_CC1: J4.A5 (CC1), R25.1
U7_CC2: J4.B5 (CC2), R26.1
U7_CHG_BTST: C24.1, U7.12 (BTST)
U7_CHG_LED: D8.2 (A), R33.2
U7_ILIM: R27.1, U7.8 (ILIM)
U7_MID: R30.1, U7.9 (MID)
U7_REGN: C25.1, R28.1, R33.1, U7.11 (REGN)
U7_STAT: D8.1 (K), U7.2 (STAT)
U7_TS: R28.2, R29.1, U7.7 (TS)
U8_BMI_SDO1: R36.1, U9.15 (SDO1)
U8_BMI_SDO2: R37.1, U9.10 (SDO2)
U8_BNO_BOOT: R34.2, U8.4 (~BOOT_LOAD_PIN)
U8_BNO_CAP: C32.1, U8.9 (CAP)
U8_BNO_RST: R35.2, U8.11 (~RESET)
UART_RTS: J1.12, R19.1
UART_RX: J1.9, R18.2
UART_TX: J1.7, R17.1
VBAT_AUX: C12.2, F2.2, J13.1, Q7.2 (S), U4.3 (EN), U4.6 (ANODE)
VBAT_CHG: C28.1, F3.2, U7.13 (BAT), U7.14 (BAT)
VBAT_F: F1.2, R1.1, R2.1
VBAT_IN: D1.2 (A2), F1.1, F3.1, J2.2
VBAT_SH: Q1.5 (D), R1.2, R3.1, R4.1
VBUS: F4.1, J4.A4 (VBUS), J4.A9 (VBUS), J4.B4 (VBUS), J4.B9 (VBUS)
VBUS_CHG: C22.1, F4.2, U7.23 (VBUS)
VPI_IN: C13.1, C14.1, C15.1, C16.1, Q7.3 (D), U4.4 (CATHODE), U5.3 (VIN)
VSERVO: C6.1, C7.1, C8.1, C9.1, C10.1, C11.1, J6.2, J7.2, J8.2, J9.2, Q3.5 (D)
VSYS: F2.1, Q2.5 (D), Q3.1 (S), Q3.2 (S), Q3.3 (S), R8.1

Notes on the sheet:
Pack input: XT30, TVS, 20 A fuse, 1 mOhm shunt, charger fuse
INA226 pack monitor (0x40)
Main switch: back-to-back AON6411, backpack switch on J5
Servo kill: AON6411 on VSERVO (GPIO26, INA226 ALERT)
STS3215 half-duplex driver (Feetech/Waveshare reference)
Servo port J6: left leg (IDs 20-24)
Servo port J7: right leg (IDs 10-14)
Servo port J8: neck chain (IDs 30-33)
Servo port J9: spare / service
VSERVO bulk, right
VSERVO bulk, left
Face board link: J12 GH 12P, J13 XH 2P fused VBAT
Pi rail: ideal diode, 470 uF hold-up, TPS56339 5.1 V, XC6206 3.3 V
USB-C 2S charger BQ25887 with balancing
IMU: BNO055 0x28 (fitted), BMI088 (not fitted)
Left foot switch J10 (GPIO22)
Right foot switch J11 (GPIO27)
Pi Zero 2 W socket (carrier, Option A)
Status LEDs (GPIO5/6), Qwiic I2C port
M2.5 holes on trunk_top's adapter bosses
Power flags

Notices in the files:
README.md:
Licence and attribution:
- The board files here (`board.json`, the `quackcore_*` blocks, the scripts) are part of the
heypcb-kicad repository.
- **Open Duck Mini** (CAD, STLs, URDF, documentation), by Antoine Pirrone (apirrone) and
contributors, is Apache License 2.0 (github.com/apirrone/Open_Duck_Mini; Onshape document
64074dfcfa379b37d8a47762). `cad/body_middle_top_usbc.stl` is derived from its
`print/body_middle_top.stl`; the change is stated in `cad/NOTICE`, and the licence is copied as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
